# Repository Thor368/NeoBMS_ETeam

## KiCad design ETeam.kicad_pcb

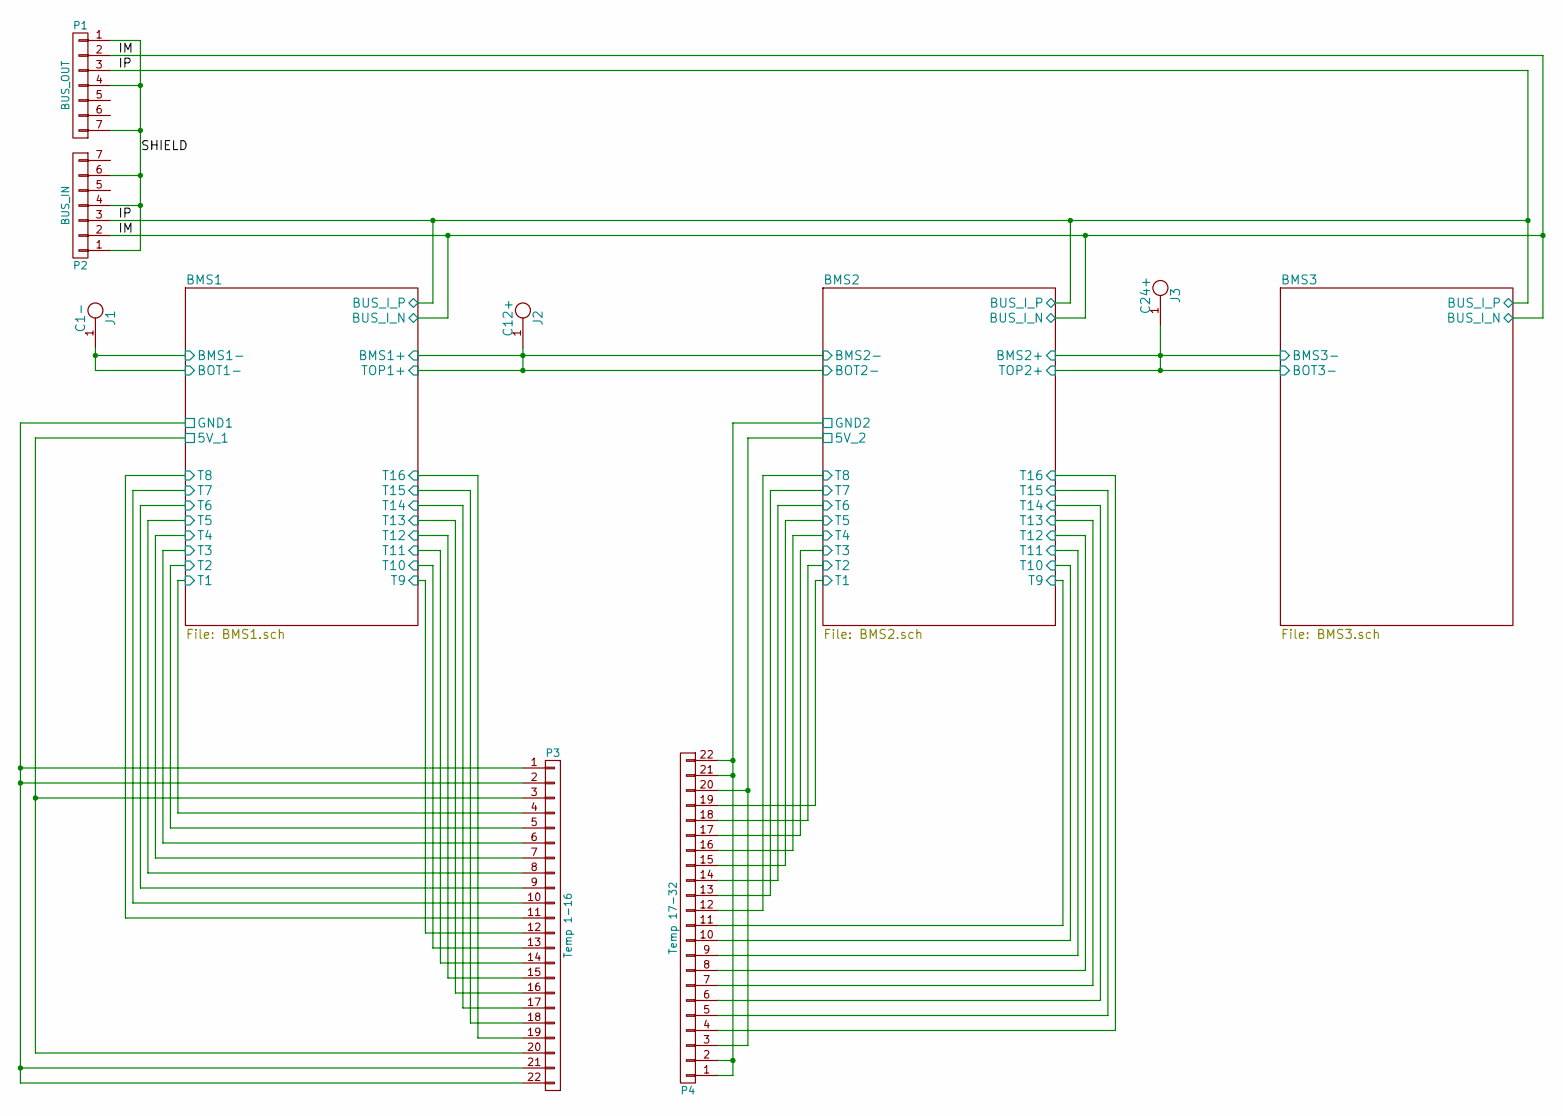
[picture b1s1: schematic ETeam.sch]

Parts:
J1: C1-; EteamPad
J2: C12+; EteamPadHole
J3: C24+; EteamPadHole
P1: BUS_OUT; Molex_0678007001
P2: BUS_IN; Molex_0678007001
P3: Temp 1-16; Ampenol_HFW22R
P4: Temp 17-32; Ampenol_HFW22R

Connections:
/BMS1/5V_1: P3.3, P3.20; also elsewhere on the board
/BMS1/BMS1+: J2.1, P4.1, P4.2, P4.21, P4.22; also elsewhere on the board
/BMS1/BMS1-: J1.1, P3.1, P3.2, P3.21, P3.22; also elsewhere on the board
/BMS1/BUS_I_N: P1.2, P2.2; also elsewhere on the board
/BMS1/BUS_I_P: P1.3, P2.3; also elsewhere on the board
/BMS1/T1: P3.4; also elsewhere on the board
/BMS1/T2: P3.5; also elsewhere on the board
/BMS1/T3: P3.6; also elsewhere on the board
/BMS1/T4: P3.7; also elsewhere on the board
/BMS1/T5: P3.8; also elsewhere on the board
/BMS1/T6: P3.9; also elsewhere on the board
/BMS1/T7: P3.10; also elsewhere on the board
/BMS1/T8: P3.11; also elsewhere on the board
/BMS1/T9: P3.12; also elsewhere on the board
/BMS1/T10: P3.13; also elsewhere on the board
/BMS1/T11: P3.14; also elsewhere on the board
/BMS1/T12: P3.15; also elsewhere on the board
/BMS1/T13: P3.16; also elsewhere on the board
/BMS1/T14: P3.17; also elsewhere on the board
/BMS1/T15: P3.18; also elsewhere on the board
/BMS1/T16: P3.19; also elsewhere on the board
/BMS2/5V_2: P4.3, P4.20; also elsewhere on the board
/BMS2/T1: P4.19; also elsewhere on the board
/BMS2/T2: P4.18; also elsewhere on the board
/BMS2/T3: P4.17; also elsewhere on the board
/BMS2/T4: P4.16; also elsewhere on the board
/BMS2/T5: P4.15; also elsewhere on the board
/BMS2/T6: P4.14; also elsewhere on the board
/BMS2/T7: P4.13; also elsewhere on the board
/BMS2/T8: P4.12; also elsewhere on the board
/BMS2/T9: P4.11; also elsewhere on the board
/BMS2/T10: P4.10; also elsewhere on the board
/BMS2/T11: P4.9; also elsewhere on the board
/BMS2/T12: P4.8; also elsewhere on the board
/BMS2/T13: P4.7; also elsewhere on the board
/BMS2/T14: P4.6; also elsewhere on the board
/BMS2/T15: P4.5; also elsewhere on the board
/BMS2/T16: P4.4; also elsewhere on the board
/SHIELD: P1.1, P1.4, P1.7, P2.1, P2.4, P2.6
GND3: J3.1; also elsewhere on the board

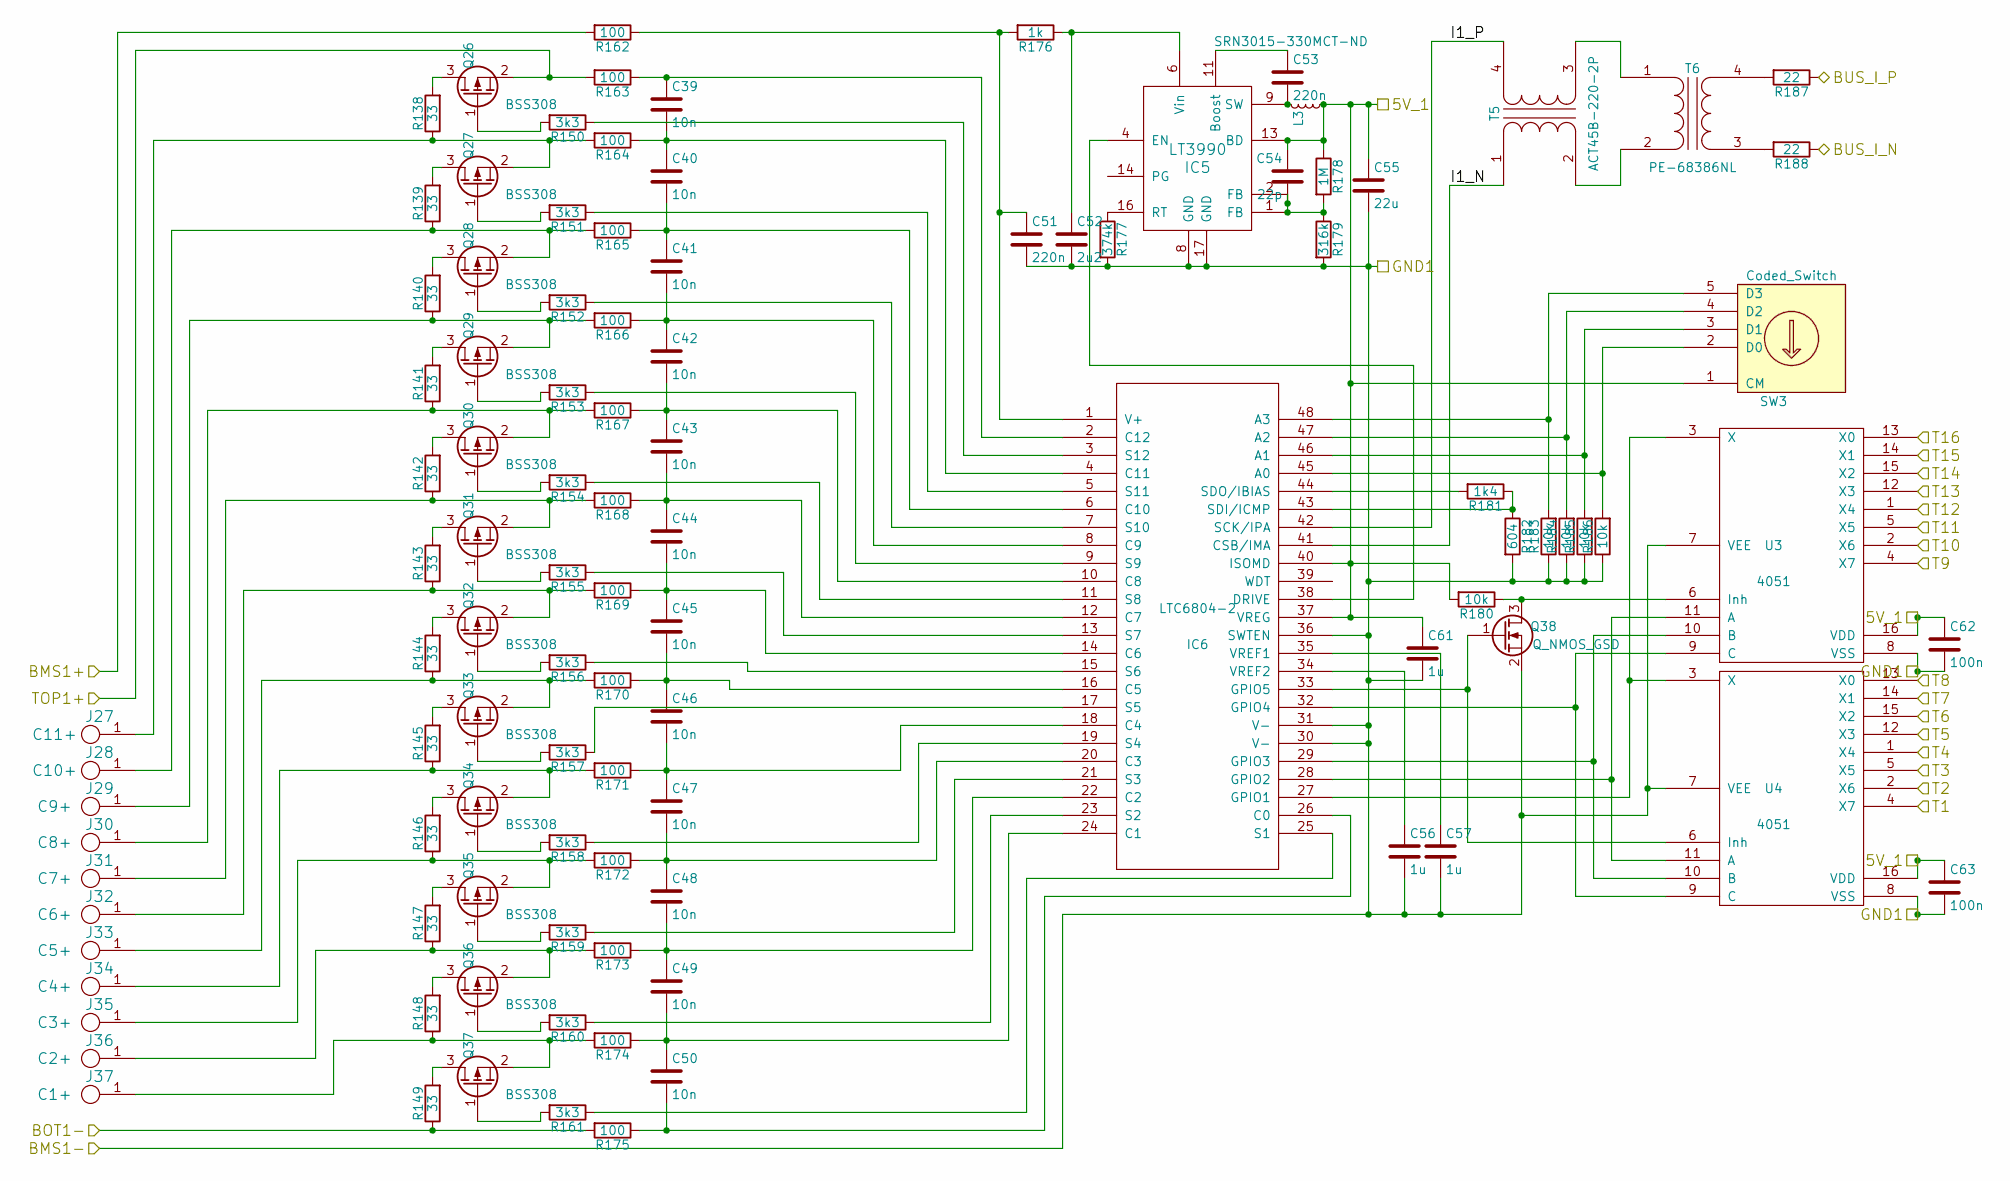
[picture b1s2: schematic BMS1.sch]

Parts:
C39, C40, C41, C42, C43, C44, C45, C46, C47, C48, C49, C50: 10n; C_0805
C51, C53: 220n; C_0805
C52: 2u2; C_1210
C54: 22p; C_0805
C55: 22u; C_0805
C56, C57, C61: 1u; C_0805
C62, C63: 100n; C_0805
IC5: LT3990; MSOP-16-1EP-VIA_3x4mm_Pitch0.5mm
IC6: LTC6804-2; TSSOP-48_6.1x12.5mm_Pitch0.5mm
J27: C11+; EteamPadHole
J28: C10+; EteamPadHole
J29: C9+; EteamPadHole
J30: C8+; EteamPadHole
J31: C7+; EteamPad
J32: C6+; EteamPadHole
J33: C5+; EteamPadHole
J34: C4+; EteamPadHole
J35: C3+; EteamPadHole
J36: C2+; EteamPadHole
J37: C1+; EteamPadHole
L3: SRN3015-330MCT-ND; SRN3015
Q26, Q27, Q28, Q29, Q30, Q31, Q32, Q33, Q34, Q35, Q36, Q37: BSS308; SOT-23
Q38: Q_NMOS_GSD; SOT-23
R138, R139, R140, R141, R142, R143, R144, R145, R146, R147, R148, R149: 33; R_2010
R150, R151, R152, R153, R154, R155, R156, R157, R158, R159, R160, R161: 3k3; R_0805
R162, R163, R164, R165, R166, R167, R168, R169, R170, R171, R172, R173, R174, R175: 100; R_0805
R176: 1k; R_0805
R177: 374k; R_0805
R178: 1M; R_0805
R179: 316k; R_0805
R180, R183, R184, R185, R186: 10k; R_0805
R181: 1k4; R_0805
R182: 604; R_0805
R187, R188: 22; R_0805
SW3: Coded_Switch; Codingswitch
T5: ACT45B-220-2P; DLW43S
T6: PE-68386NL
U3, U4: 4051; SOIC-16_3.9x9.9mm_Pitch1.27mm

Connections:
/BMS1/5V_1: C54.1, C55.1, C61.1, C62.1, C63.1, IC5.13 (BD), IC6.37 (VREG), IC6.40 (ISOMD), L3.2, R178.1, R180.2, SW3.1 (CM), U3.16 (VDD), U4.16 (VDD); also elsewhere on the board
/BMS1/BMS1+: Q26.2 (S), R162.2, R163.2; also elsewhere on the board
/BMS1/BMS1-: C51.2, C52.2, C55.2, C56.2, C57.2, C61.2, C62.2, C63.2, IC5.8 (GND), IC5.17 (GND), IC6.30 (V-), IC6.31 (V-), IC6.36 (SWTEN), Q38.2 (S), R149.1, R175.2, R177.2, R179.2, R182.2, R183.1, R184.1, R185.1, R186.1, U3.7 (VEE), U3.8 (VSS), U4.7 (VEE), U4.8 (VSS); also elsewhere on the board
/BMS1/BUS_I_N: R188.1; also elsewhere on the board
/BMS1/BUS_I_P: R187.1; also elsewhere on the board
/BMS1/I1_N: IC6.41 (CSB/IMA), T5.1 (AA)
/BMS1/I1_P: IC6.42 (SCK/IPA), T5.4 (SB)
/BMS1/T1: U4.4 (X7); also elsewhere on the board
/BMS1/T2: U4.2 (X6); also elsewhere on the board
/BMS1/T3: U4.5 (X5); also elsewhere on the board
/BMS1/T4: U4.1 (X4); also elsewhere on the board
/BMS1/T5: U4.12 (X3); also elsewhere on the board
/BMS1/T6: U4.15 (X2); also elsewhere on the board
/BMS1/T7: U4.14 (X1); also elsewhere on the board
/BMS1/T8: U4.13 (X0); also elsewhere on the board
/BMS1/T9: U3.4 (X7); also elsewhere on the board
/BMS1/T10: U3.2 (X6); also elsewhere on the board
/BMS1/T11: U3.5 (X5); also elsewhere on the board
/BMS1/T12: U3.1 (X4); also elsewhere on the board
/BMS1/T13: U3.12 (X3); also elsewhere on the board
/BMS1/T14: U3.15 (X2); also elsewhere on the board
/BMS1/T15: U3.14 (X1); also elsewhere on the board
/BMS1/T16: U3.13 (X0); also elsewhere on the board
unnamed: C39.1, IC6.2 (C12), R163.1
unnamed: C39.2, C40.1, IC6.4 (C11), R164.1
unnamed: C40.2, C41.1, IC6.6 (C10), R165.1
unnamed: C41.2, C42.1, IC6.8 (C9), R166.1
unnamed: C42.2, C43.1, IC6.10 (C8), R167.1
unnamed: C43.2, C44.1, IC6.12 (C7), R168.1
unnamed: C44.2, C45.1, IC6.14 (C6), R169.1
unnamed: C45.2, C46.1, IC6.16 (C5), R170.1
unnamed: C46.2, C47.1, IC6.18 (C4), R171.1
unnamed: C47.2, C48.1, IC6.20 (C3), R172.1
unnamed: C48.2, C49.1, IC6.22 (C2), R173.1
unnamed: C49.2, C50.1, IC6.24 (C1), R174.1
unnamed: C50.2, IC6.26 (C0), R175.1
unnamed: C51.1, IC6.1 (V+), R162.1, R176.2
unnamed: C52.1, IC5.6 (Vin), R176.1
unnamed: C53.1, IC5.11 (Boost)
unnamed: C53.2, IC5.9 (SW), L3.1
unnamed: C54.2, IC5.1 (FB), IC5.2 (FB), R178.2, R179.1
unnamed: C56.1, IC6.34 (VREF2)
unnamed: C57.1, IC6.35 (VREF1)
unnamed: IC5.4 (EN), IC6.38 (DRIVE)
unnamed: IC5.16 (RT), R177.1
unnamed: IC6.3 (S12), R150.1
unnamed: IC6.5 (S11), R151.1
unnamed: IC6.7 (S10), R152.1
unnamed: IC6.9 (S9), R153.1
unnamed: IC6.11 (S8), R154.1
unnamed: IC6.13 (S7), R155.1
unnamed: IC6.15 (S6), R156.1
unnamed: IC6.17 (S5), R157.1
unnamed: IC6.19 (S4), R158.1
unnamed: IC6.21 (S3), R159.1
unnamed: IC6.23 (S2), R160.1
unnamed: IC6.25 (S1), R161.1
unnamed: IC6.27 (GPIO1), U3.3 (X), U4.3 (X)
unnamed: IC6.28 (GPIO2), U3.11 (A), U4.11 (A)
unnamed: IC6.29 (GPIO3), U3.10 (B), U4.10 (B)
unnamed: IC6.32 (GPIO4), U3.9 (C), U4.9 (C)
unnamed: IC6.33 (GPIO5), Q38.1 (G), U4.6 (Inh)
unnamed: IC6.43 (SDI/ICMP), R181.1, R182.1
unnamed: IC6.44 (SDO/IBIAS), R181.2
unnamed: IC6.45 (A0), R186.2, SW3.2 (D0)
unnamed: IC6.46 (A1), R185.2, SW3.3 (D1)
unnamed: IC6.47 (A2), R184.2, SW3.4 (D2)
unnamed: IC6.48 (A3), R183.2, SW3.5 (D3)
unnamed: J27.1, Q27.2 (S), R138.1, R164.2
unnamed: J28.1, Q28.2 (S), R139.1, R165.2
unnamed: J29.1, Q29.2 (S), R140.1, R166.2
unnamed: J30.1, Q30.2 (S), R141.1, R167.2
unnamed: J31.1, Q31.2 (S), R142.1, R168.2
unnamed: J32.1, Q32.2 (S), R143.1, R169.2
unnamed: J33.1, Q33.2 (S), R144.1, R170.2
unnamed: J34.1, Q34.2 (S), R145.1, R171.2
unnamed: J35.1, Q35.2 (S), R146.1, R172.2
unnamed: J36.1, Q36.2 (S), R147.1, R173.2
unnamed: J37.1, Q37.2 (S), R148.1, R174.2
unnamed: Q26.1 (G), R150.2
unnamed: Q26.3 (D), R138.2
unnamed: Q27.1 (G), R151.2
unnamed: Q27.3 (D), R139.2
unnamed: Q28.1 (G), R152.2
unnamed: Q28.3 (D), R140.2
unnamed: Q29.1 (G), R153.2
unnamed: Q29.3 (D), R141.2
unnamed: Q30.1 (G), R154.2
unnamed: Q30.3 (D), R142.2
unnamed: Q31.1 (G), R155.2
unnamed: Q31.3 (D), R143.2
unnamed: Q32.1 (G), R156.2
unnamed: Q32.3 (D), R144.2
unnamed: Q33.1 (G), R157.2
unnamed: Q33.3 (D), R145.2
unnamed: Q34.1 (G), R158.2
unnamed: Q34.3 (D), R146.2
unnamed: Q35.1 (G), R159.2
unnamed: Q35.3 (D), R147.2
unnamed: Q36.1 (G), R160.2
unnamed: Q36.3 (D), R148.2
unnamed: Q37.1 (G), R161.2
unnamed: Q37.3 (D), R149.2
unnamed: Q38.3 (D), R180.1, U3.6 (Inh)
unnamed: R187.2, T6.4 (SB)
unnamed: R188.2, T6.3 (SA)
unnamed: T5.2 (AB), T6.2 (AB)
unnamed: T5.3 (SA), T6.1 (AA)

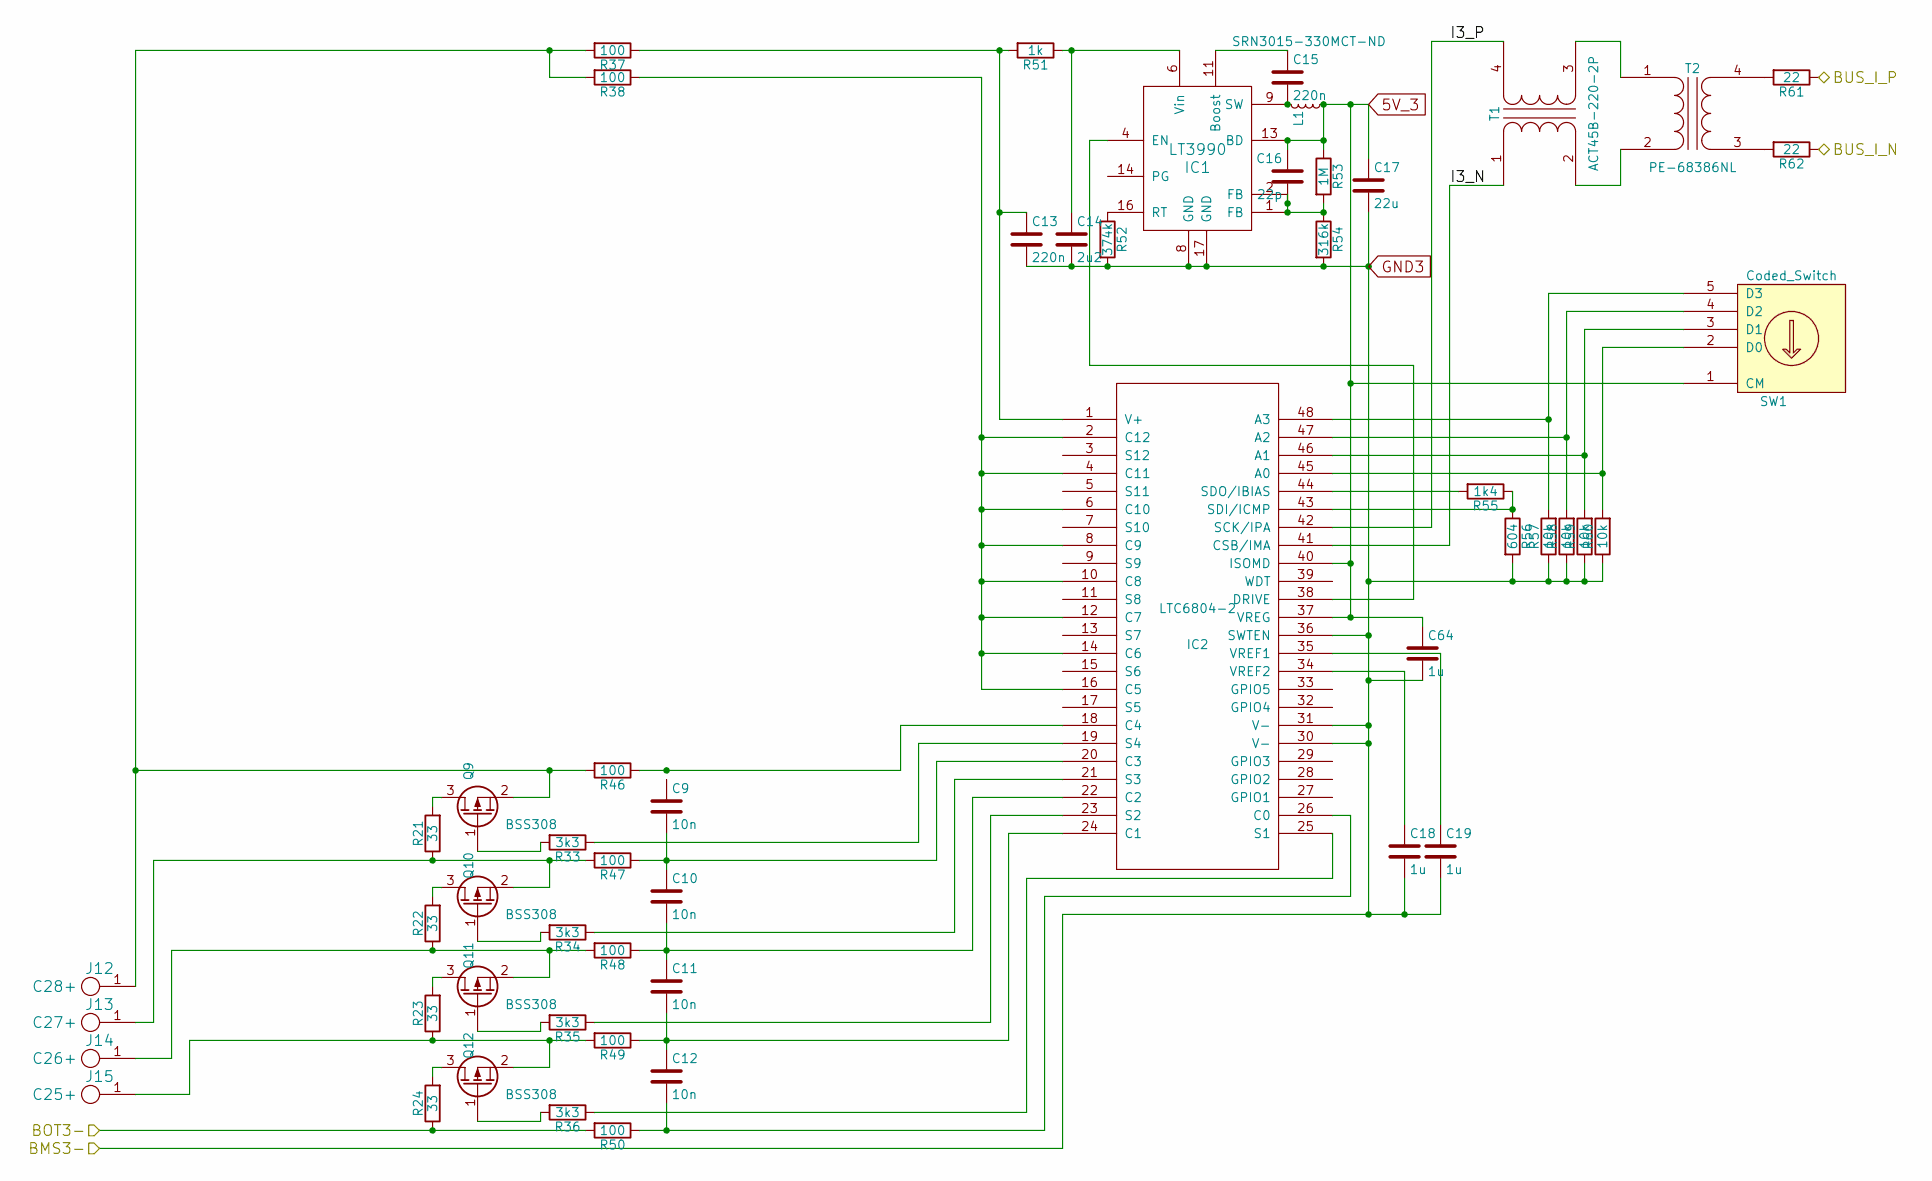
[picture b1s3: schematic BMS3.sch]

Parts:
C9, C10, C11, C12: 10n; C_0805
C13, C15: 220n; C_0805
C14: 2u2; C_1210
C16: 22p; C_0805
C17: 22u; C_0805
C18, C19, C64: 1u; C_0805
IC1: LT3990; MSOP-16-1EP-VIA_3x4mm_Pitch0.5mm
IC2: LTC6804-2; TSSOP-48_6.1x12.5mm_Pitch0.5mm
J12: C28+; EteamPad
J13: C27+; EteamPadHole
J14: C26+; EteamPadHole
J15: C25+; EteamPadHole
L1: SRN3015-330MCT-ND; SRN3015
Q9, Q10, Q11, Q12: BSS308; SOT-23
R21, R22, R23, R24: 33; R_2010
R33, R34, R35, R36: 3k3; R_0805
R37, R38, R46, R47, R48, R49, R50: 100; R_0805
R51: 1k; R_0805
R52: 374k; R_0805
R53: 1M; R_0805
R54: 316k; R_0805
R55: 1k4; R_0805
R56: 604; R_0805
R57, R58, R59, R60: 10k; R_0805
R61, R62: 22; R_0805
SW1: Coded_Switch; Codingswitch
T1: ACT45B-220-2P; DLW43S
T2: PE-68386NL

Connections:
5V_3: C16.1, C17.1, C64.1, IC1.13 (BD), IC2.37 (VREG), IC2.40 (ISOMD), L1.2, R53.1, SW1.1 (CM)
/BMS1/BUS_I_N: R62.1; also elsewhere on the board
/BMS1/BUS_I_P: R61.1; also elsewhere on the board
/BMS3/I3_N: IC2.41 (CSB/IMA), T1.1 (AA)
/BMS3/I3_P: IC2.42 (SCK/IPA), T1.4 (SB)
GND3: C13.2, C14.2, C17.2, C18.2, C19.2, C64.2, IC1.8 (GND), IC1.17 (GND), IC2.30 (V-), IC2.31 (V-), IC2.36 (SWTEN), R24.1, R50.2, R52.2, R54.2, R56.2, R57.1, R58.1, R59.1, R60.1; also elsewhere on the board
unnamed: C9.2, C10.1, IC2.20 (C3), R47.1
unnamed: C10.2, C11.1, IC2.22 (C2), R48.1
unnamed: C11.2, C12.1, IC2.24 (C1), R49.1
unnamed: C12.2, IC2.26 (C0), R50.1
unnamed: C13.1, IC2.1 (V+), R37.1, R51.2
unnamed: C14.1, IC1.6 (Vin), R51.1
unnamed: C15.1, IC1.11 (Boost)
unnamed: C15.2, IC1.9 (SW), L1.1
unnamed: C16.2, IC1.1 (FB), IC1.2 (FB), R53.2, R54.1
unnamed: C18.1, IC2.34 (VREF2)
unnamed: C19.1, IC2.35 (VREF1)
unnamed: IC1.4 (EN), IC2.38 (DRIVE)
unnamed: IC1.16 (RT), R52.1
unnamed: IC2.2 (C12), IC2.4 (C11), IC2.6 (C10), IC2.8 (C9), IC2.10 (C8), IC2.12 (C7), IC2.14 (C6), IC2.16 (C5), R38.1
unnamed: IC2.18 (C4), R46.1
unnamed: IC2.19 (S4), R33.1
unnamed: IC2.21 (S3), R34.1
unnamed: IC2.23 (S2), R35.1
unnamed: IC2.25 (S1), R36.1
unnamed: IC2.43 (SDI/ICMP), R55.1, R56.1
unnamed: IC2.44 (SDO/IBIAS), R55.2
unnamed: IC2.45 (A0), R60.2, SW1.2 (D0)
unnamed: IC2.46 (A1), R59.2, SW1.3 (D1)
unnamed: IC2.47 (A2), R58.2, SW1.4 (D2)
unnamed: IC2.48 (A3), R57.2, SW1.5 (D3)
unnamed: J12.1, Q9.2 (S), R37.2, R38.2, R46.2
unnamed: J13.1, Q10.2 (S), R21.1, R47.2
unnamed: J14.1, Q11.2 (S), R22.1, R48.2
unnamed: J15.1, Q12.2 (S), R23.1, R49.2
unnamed: Q9.1 (G), R33.2
unnamed: Q9.3 (D), R21.2
unnamed: Q10.1 (G), R34.2
unnamed: Q10.3 (D), R22.2
unnamed: Q11.1 (G), R35.2
unnamed: Q11.3 (D), R23.2
unnamed: Q12.1 (G), R36.2
unnamed: Q12.3 (D), R24.2
unnamed: R61.2, T2.4 (SB)
unnamed: R62.2, T2.3 (SA)
unnamed: T1.2 (AB), T2.2 (AB)
unnamed: T1.3 (SA), T2.1 (AA)

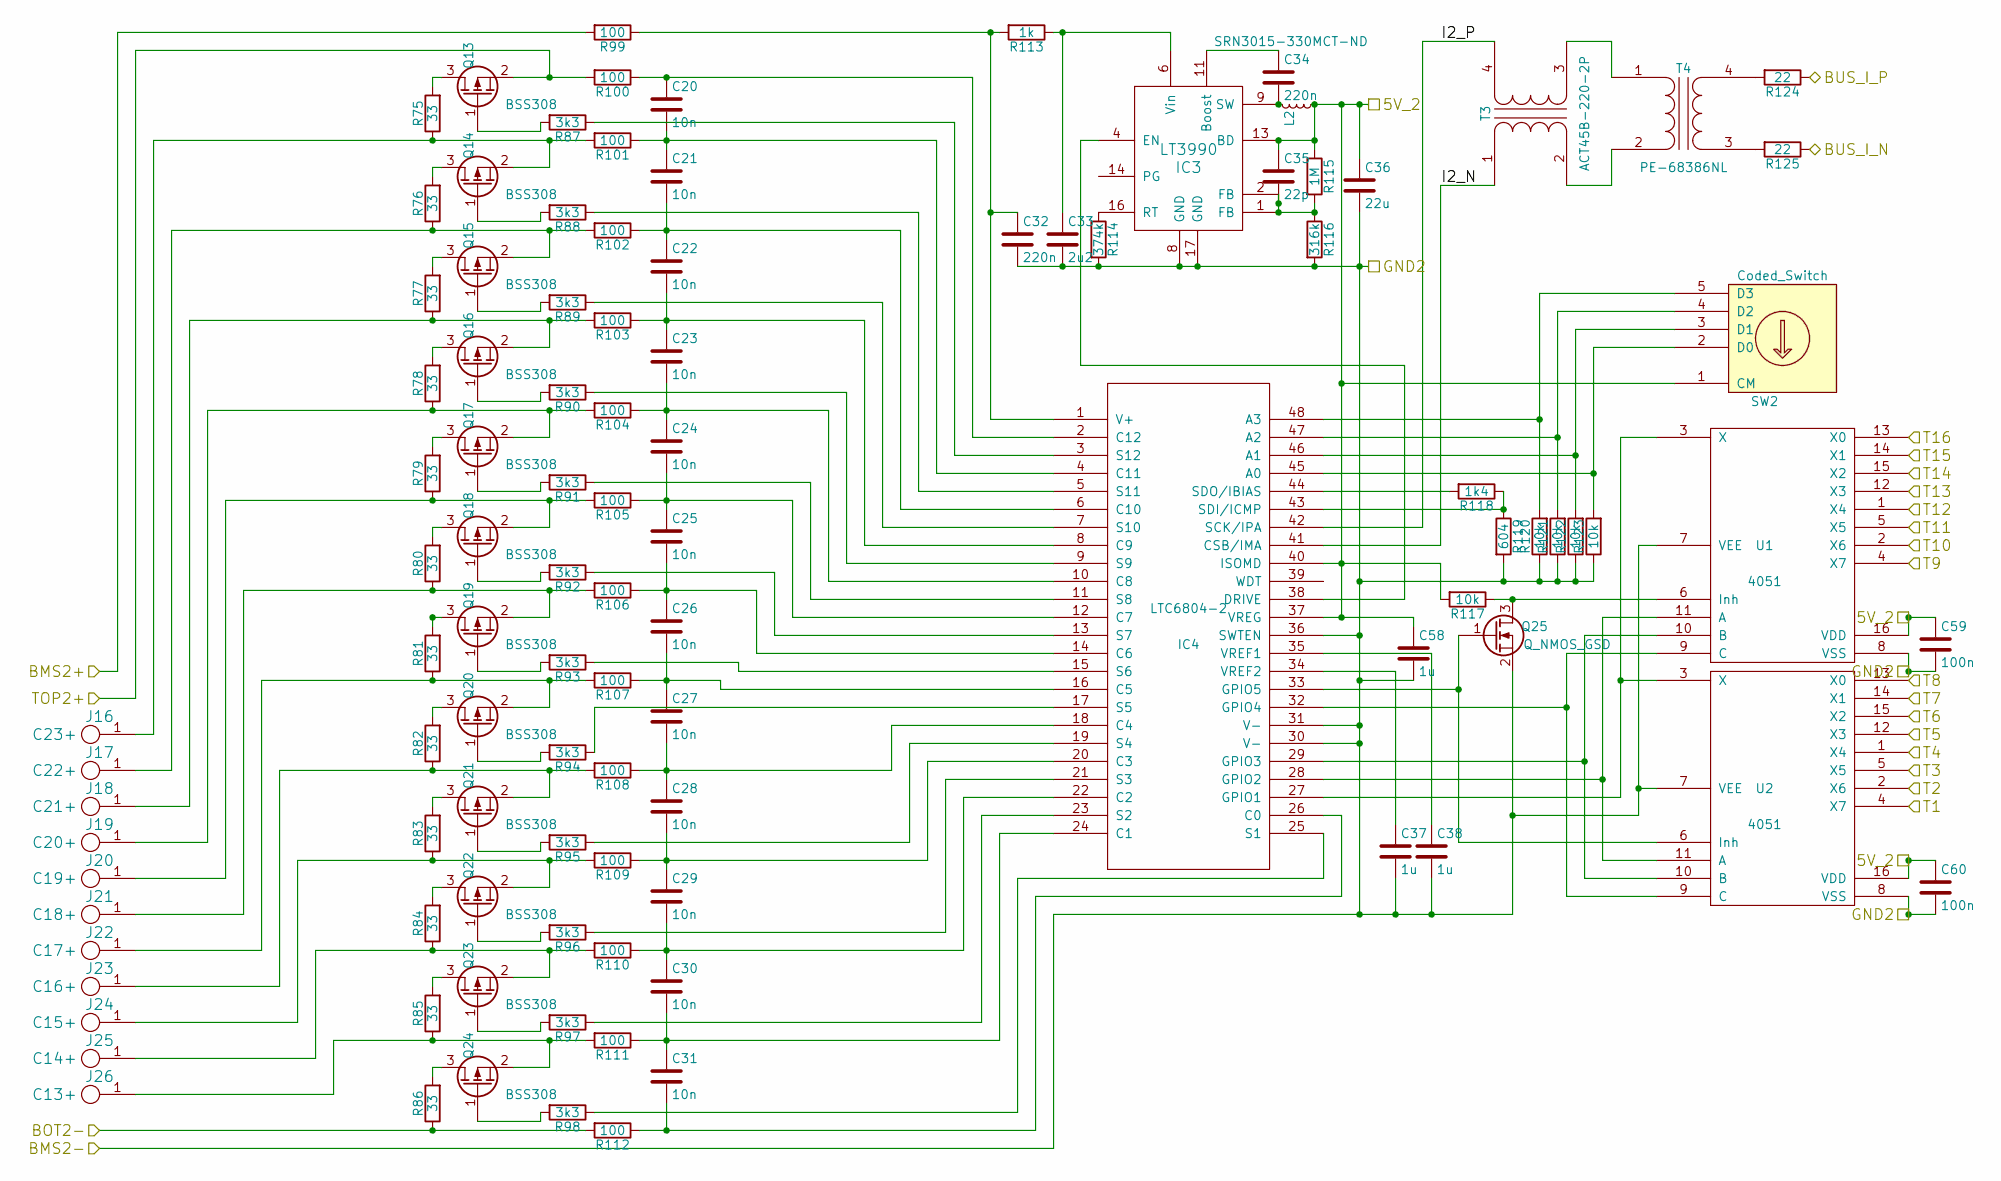
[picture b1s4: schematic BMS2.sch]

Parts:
C20, C21, C22, C23, C24, C25, C26, C27, C28, C29, C30, C31: 10n; C_0805
C32, C34: 220n; C_0805
C33: 2u2; C_1210
C35: 22p; C_0805
C36: 22u; C_0805
C37, C38, C58: 1u; C_0805
C59, C60: 100n; C_0805
IC3: LT3990; MSOP-16-1EP-VIA_3x4mm_Pitch0.5mm
IC4: LTC6804-2; TSSOP-48_6.1x12.5mm_Pitch0.5mm
J16: C23+; EteamPadHole
J17: C22+; EteamPadHole
J18: C21+; EteamPad
J19: C20+; EteamPadHole
J20: C19+; EteamPadHole
J21: C18+; EteamPadHole
J22: C17+; EteamPadHole
J23: C16+; EteamPadHole
J24: C15+; EteamPadHole
J25: C14+; EteamPad
J26: C13+; EteamPadHole
L2: SRN3015-330MCT-ND; SRN3015
Q13, Q14, Q15, Q16, Q17, Q18, Q19, Q20, Q21, Q22, Q23, Q24: BSS308; SOT-23
Q25: Q_NMOS_GSD; SOT-23
R75, R76, R77, R78, R79, R80, R81, R82, R83, R84, R85, R86: 33; R_2010
R87, R88, R89, R90, R91, R92, R93, R94, R95, R96, R97, R98: 3k3; R_0805
R99, R100, R101, R102, R103, R104, R105, R106, R107, R108, R109, R110, R111, R112: 100; R_0805
R113: 1k; R_0805
R114: 374k; R_0805
R115: 1M; R_0805
R116: 316k; R_0805
R117, R120, R121, R122, R123: 10k; R_0805
R118: 1k4; R_0805
R119: 604; R_0805
R124, R125: 22; R_0805
SW2: Coded_Switch; Codingswitch
T3: ACT45B-220-2P; DLW43S
T4: PE-68386NL
U1, U2: 4051; SOIC-16_3.9x9.9mm_Pitch1.27mm

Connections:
/BMS1/BMS1+: C32.2, C33.2, C36.2, C37.2, C38.2, C58.2, C59.2, C60.2, IC3.8 (GND), IC3.17 (GND), IC4.30 (V-), IC4.31 (V-), IC4.36 (SWTEN), Q25.2 (S), R86.1, R112.2, R114.2, R116.2, R119.2, R120.1, R121.1, R122.1, R123.1, U1.7 (VEE), U1.8 (VSS), U2.7 (VEE), U2.8 (VSS); also elsewhere on the board
/BMS1/BUS_I_N: R125.1; also elsewhere on the board
/BMS1/BUS_I_P: R124.1; also elsewhere on the board
/BMS2/5V_2: C35.1, C36.1, C58.1, C59.1, C60.1, IC3.13 (BD), IC4.37 (VREG), IC4.40 (ISOMD), L2.2, R115.1, R117.2, SW2.1 (CM), U1.16 (VDD), U2.16 (VDD); also elsewhere on the board
/BMS2/I2_N: IC4.41 (CSB/IMA), T3.1 (AA)
/BMS2/I2_P: IC4.42 (SCK/IPA), T3.4 (SB)
/BMS2/T1: U2.4 (X7); also elsewhere on the board
/BMS2/T2: U2.2 (X6); also elsewhere on the board
/BMS2/T3: U2.5 (X5); also elsewhere on the board
/BMS2/T4: U2.1 (X4); also elsewhere on the board
/BMS2/T5: U2.12 (X3); also elsewhere on the board
/BMS2/T6: U2.15 (X2); also elsewhere on the board
/BMS2/T7: U2.14 (X1); also elsewhere on the board
/BMS2/T8: U2.13 (X0); also elsewhere on the board
/BMS2/T9: U1.4 (X7); also elsewhere on the board
/BMS2/T10: U1.2 (X6); also elsewhere on the board
/BMS2/T11: U1.5 (X5); also elsewhere on the board
/BMS2/T12: U1.1 (X4); also elsewhere on the board
/BMS2/T13: U1.12 (X3); also elsewhere on the board
/BMS2/T14: U1.15 (X2); also elsewhere on the board
/BMS2/T15: U1.14 (X1); also elsewhere on the board
/BMS2/T16: U1.13 (X0); also elsewhere on the board
GND3: Q13.2 (S), R99.2, R100.2; also elsewhere on the board
unnamed: C20.1, IC4.2 (C12), R100.1
unnamed: C20.2, C21.1, IC4.4 (C11), R101.1
unnamed: C21.2, C22.1, IC4.6 (C10), R102.1
unnamed: C22.2, C23.1, IC4.8 (C9), R103.1
unnamed: C23.2, C24.1, IC4.10 (C8), R104.1
unnamed: C24.2, C25.1, IC4.12 (C7), R105.1
unnamed: C25.2, C26.1, IC4.14 (C6), R106.1
unnamed: C26.2, C27.1, IC4.16 (C5), R107.1
unnamed: C27.2, C28.1, IC4.18 (C4), R108.1
unnamed: C28.2, C29.1, IC4.20 (C3), R109.1
unnamed: C29.2, C30.1, IC4.22 (C2), R110.1
unnamed: C30.2, C31.1, IC4.24 (C1), R111.1
unnamed: C31.2, IC4.26 (C0), R112.1
unnamed: C32.1, IC4.1 (V+), R99.1, R113.2
unnamed: C33.1, IC3.6 (Vin), R113.1
unnamed: C34.1, IC3.11 (Boost)
unnamed: C34.2, IC3.9 (SW), L2.1
unnamed: C35.2, IC3.1 (FB), IC3.2 (FB), R115.2, R116.1
unnamed: C37.1, IC4.34 (VREF2)
unnamed: C38.1, IC4.35 (VREF1)
unnamed: IC3.4 (EN), IC4.38 (DRIVE)
unnamed: IC3.16 (RT), R114.1
unnamed: IC4.3 (S12), R87.1
unnamed: IC4.5 (S11), R88.1
unnamed: IC4.7 (S10), R89.1
unnamed: IC4.9 (S9), R90.1
unnamed: IC4.11 (S8), R91.1
unnamed: IC4.13 (S7), R92.1
unnamed: IC4.15 (S6), R93.1
unnamed: IC4.17 (S5), R94.1
unnamed: IC4.19 (S4), R95.1
unnamed: IC4.21 (S3), R96.1
unnamed: IC4.23 (S2), R97.1
unnamed: IC4.25 (S1), R98.1
unnamed: IC4.27 (GPIO1), U1.3 (X), U2.3 (X)
unnamed: IC4.28 (GPIO2), U1.11 (A), U2.11 (A)
unnamed: IC4.29 (GPIO3), U1.10 (B), U2.10 (B)
unnamed: IC4.32 (GPIO4), U1.9 (C), U2.9 (C)
unnamed: IC4.33 (GPIO5), Q25.1 (G), U2.6 (Inh)
unnamed: IC4.43 (SDI/ICMP), R118.1, R119.1
unnamed: IC4.44 (SDO/IBIAS), R118.2
unnamed: IC4.45 (A0), R123.2, SW2.2 (D0)
unnamed: IC4.46 (A1), R122.2, SW2.3 (D1)
unnamed: IC4.47 (A2), R121.2, SW2.4 (D2)
unnamed: IC4.48 (A3), R120.2, SW2.5 (D3)
unnamed: J16.1, Q14.2 (S), R75.1, R101.2
unnamed: J17.1, Q15.2 (S), R76.1, R102.2
unnamed: J18.1, Q16.2 (S), R77.1, R103.2
unnamed: J19.1, Q17.2 (S), R78.1, R104.2
unnamed: J20.1, Q18.2 (S), R79.1, R105.2
unnamed: J21.1, Q19.2 (S), R80.1, R106.2
unnamed: J22.1, Q20.2 (S), R81.1, R107.2
unnamed: J23.1, Q21.2 (S), R82.1, R108.2
unnamed: J24.1, Q22.2 (S), R83.1, R109.2
unnamed: J25.1, Q23.2 (S), R84.1, R110.2
unnamed: J26.1, Q24.2 (S), R85.1, R111.2
unnamed: Q13.1 (G), R87.2
unnamed: Q13.3 (D), R75.2
unnamed: Q14.1 (G), R88.2
unnamed: Q14.3 (D), R76.2
unnamed: Q15.1 (G), R89.2
unnamed: Q15.3 (D), R77.2
unnamed: Q16.1 (G), R90.2
unnamed: Q16.3 (D), R78.2
unnamed: Q17.1 (G), R91.2
unnamed: Q17.3 (D), R79.2
unnamed: Q18.1 (G), R92.2
unnamed: Q18.3 (D), R80.2
unnamed: Q19.1 (G), R93.2
unnamed: Q19.3 (D), R81.2
unnamed: Q20.1 (G), R94.2
unnamed: Q20.3 (D), R82.2
unnamed: Q21.1 (G), R95.2
unnamed: Q21.3 (D), R83.2
unnamed: Q22.1 (G), R96.2
unnamed: Q22.3 (D), R84.2
unnamed: Q23.1 (G), R97.2
unnamed: Q23.3 (D), R85.2
unnamed: Q24.1 (G), R98.2
unnamed: Q24.3 (D), R86.2
unnamed: Q25.3 (D), R117.1, U1.6 (Inh)
unnamed: R124.2, T4.4 (SB)
unnamed: R125.2, T4.3 (SA)
unnamed: T3.2 (AB), T4.2 (AB)
unnamed: T3.3 (SA), T4.1 (AA)

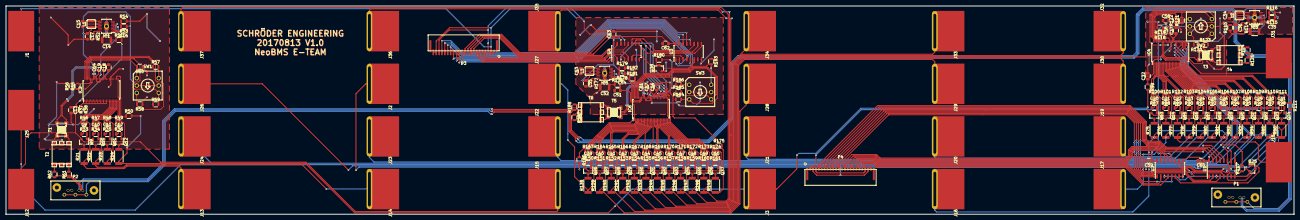
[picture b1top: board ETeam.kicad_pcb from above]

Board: 2 copper layers, 445.3 x 72.0 mm, 270 parts (0 on the bottom side), 258 nets.

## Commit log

2017-12-16 - - release candidate 1
2017-12-16 - changed the connectors for the temperature sensors
